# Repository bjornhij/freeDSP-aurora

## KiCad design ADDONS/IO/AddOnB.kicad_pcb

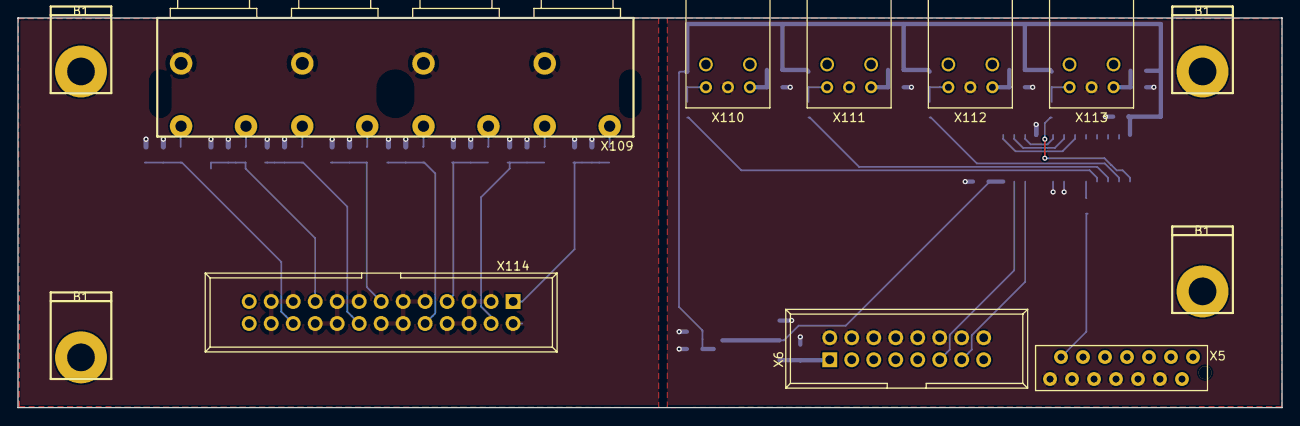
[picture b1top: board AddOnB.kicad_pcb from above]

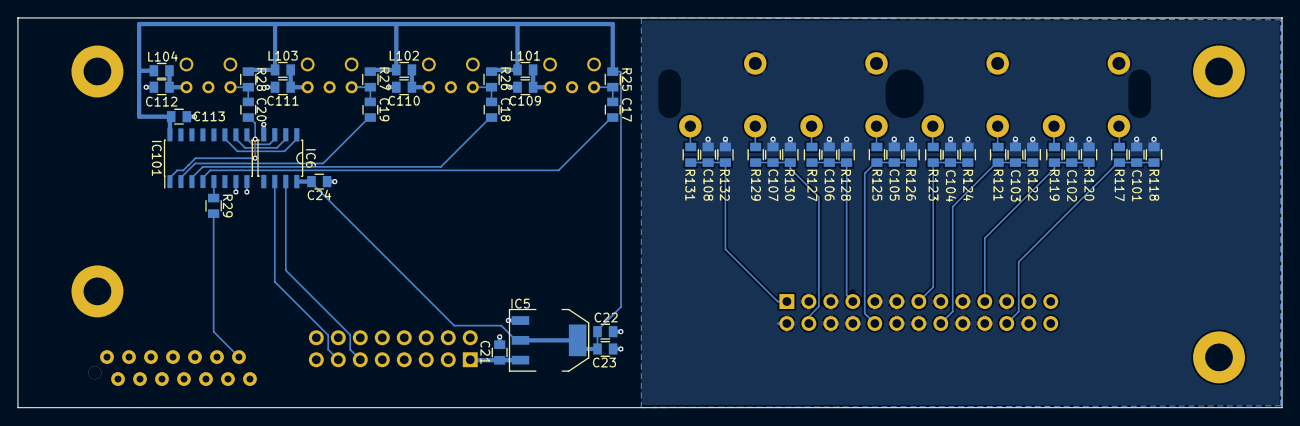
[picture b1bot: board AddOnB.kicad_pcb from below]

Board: 2 copper layers, 146.0 x 45.0 mm, 61 parts (49 on the bottom side), 38 nets.

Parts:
B1, B1#2, B1#3, B1#4: Montagewinkel
C17, C18, C19, C20: CAP_10n0_50V_X7R_0805; C0805-X7R
C21, C23: CAP_10u0_25V_X5R_0805; C0805-X7R
C22, C24, C109, C110, C111, C112, C113: CAP_100n_50V_X7R_0805; C0805-X7R
C101, C102, C103, C104, C105, C106, C107, C108: CAP_100p_50V_C0G_NP0_0805; C0805-X7R
IC5: IC_NCP1117LPST33; SOT223
IC6: PCA9536D; SOIC8_3.9x4.9mm_Pitch1.27mm
IC101: 74HC251; SOIC-16_3.9x9.9mm_P1.27mm
L101, L102, L103, L104: 47u0; C0805-X7R
R25, R26, R27, R28: RES_10K0_1%_0.125W_Thick_0805; C0805-RES
R29: RES_33R0_1%_0.125W_Thick_0805; C0805-RES
R117, R119, R121, R123, R125, R127, R129, R131: RES_100R_1%_0.25W_Thin_0805; C0805-RES
R118, R120, R122, R124, R126, R128, R130, R132: RES_220K_1%_0.125W_Thick_0805; C0805-RES
X5: MicroMatch14; MM-14G
X6: HDR_02x08; IDC2x8_Pitch2.54mm
X109: CONN_RCA_02x04; PJRAS4X2U01
X110, X111, X112, X113: PLR135_T10
X114: CON_IDC26; IDC26

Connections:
+3V3: C22.1, C23.1, C24.2, C113.2, IC5.2, IC5.4, IC6.8, IC101.16, L101.1, L102.1, L103.1, L104.1, R25.2, R26.2, R27.2, R28.2
+12V: C21.1, IC5.3, X6.1
/AIN1+: C101.1, R117.2, R118.2, X114.22
/AIN2+: C102.1, R119.2, R120.2, X114.19
/AIN3+: C103.1, R121.2, R122.2, X114.16
/AIN4+: C104.1, R123.2, R124.2, X114.13
/AIN5+: C105.1, R125.2, R126.2, X114.10
/AIN6+: C106.1, R127.2, R128.2, X114.7
/AIN7+: C107.1, R129.2, R130.2, X114.4
/AIN8+: C108.1, R131.2, R132.2, X114.1
/SCL: IC6.6, X6.13
/SDA: IC6.7, X6.11
/SPDIF_RX: R29.2, X5.13
GND: C21.2, C22.2, C23.2, C24.1, C101.2, C102.2, C103.2, C104.2, C105.2, C106.2, C107.2, C108.2, C109.2, C110.2, C111.2, C112.2, C113.1, IC5.1, IC6.4, IC101.7, IC101.8, R118.1, R120.1, R122.1, R124.1, R126.1, R128.1, R130.1, R132.1, X5.4, X5.6, X5.8, X5.10, X5.12, X5.14, X6.2, X6.4, X6.6, X6.8, X6.10, X6.12, X6.14, X6.16, X109.3A, X109.3B, X109.3C, X109.3D, X110.2, X111.2, X112.2, X113.2, X114.2, X114.3, X114.5, X114.6, X114.8, X114.9, X114.11, X114.12, X114.14, X114.15, X114.17, X114.18, X114.20, X114.21, X114.23, X114.24
unnamed: C17.1, R25.1, X110.3
unnamed: C17.2, IC101.4
unnamed: C18.1, R26.1, X111.3
unnamed: C18.2, IC101.3
unnamed: C19.1, R27.1, X112.3
unnamed: C19.2, IC101.2
unnamed: C20.1, R28.1, X113.3
unnamed: C20.2, IC101.1
unnamed: C109.1, L101.2, X110.1
unnamed: C110.1, L102.2, X111.1
unnamed: C111.1, L103.2, X112.1
unnamed: C112.1, L104.2, X113.1
unnamed: IC101.5, R29.1
unnamed: IC6.3, IC101.9
unnamed: IC6.2, IC101.10
unnamed: IC6.1, IC101.11
unnamed: R117.1, X109.2A
unnamed: R119.1, X109.1A
unnamed: R121.1, X109.2B
unnamed: R123.1, X109.1B
unnamed: R125.1, X109.2C
unnamed: R127.1, X109.1C
unnamed: R129.1, X109.2D
unnamed: R131.1, X109.1D

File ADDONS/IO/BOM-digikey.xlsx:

Reference | Value | Footprint | Datasheet | Manufacturer | pn | Value1 | Value2 | digikey
X5 | MicroMatch14 | rklib:MM-14G | ~ | TE Connectivity AMP Connectors | 1-215079-4 | MicroMatch-14 | -
X6 | HDR_02x08 | rklib:IDC2x8_Pitch2.54mm | ~ | On Shore Technology Inc. | 302-S161
X114 | CON_IDC26 | rklib:IDC26 | ~ | Bud Industries | BC-32677 | IDC26 |  | 377-2269-ND
C101 | CAP_100p_50V_C0G_NP0_0805 | rklib:C0805-X7R |  | KEMET | C0805C101J5GACTU | 100p | 5% 50V C0G/NP0 | 399-1122-1-ND
C102 | CAP_100p_50V_C0G_NP0_0805 | rklib:C0805-X7R |  | KEMET | C0805C101J5GACTU | 100p | 5% 50V C0G/NP0 | 399-1122-1-ND
C103 | CAP_100p_50V_C0G_NP0_0805 | rklib:C0805-X7R |  | KEMET | C0805C101J5GACTU | 100p | 5% 50V C0G/NP0 | 399-1122-1-ND
C104 | CAP_100p_50V_C0G_NP0_0805 | rklib:C0805-X7R |  | KEMET | C0805C101J5GACTU | 100p | 5% 50V C0G/NP0 | 399-1122-1-ND
C105 | CAP_100p_50V_C0G_NP0_0805 | rklib:C0805-X7R |  | KEMET | C0805C101J5GACTU | 100p | 5% 50V C0G/NP0 | 399-1122-1-ND
C106 | CAP_100p_50V_C0G_NP0_0805 | rklib:C0805-X7R |  | KEMET | C0805C101J5GACTU | 100p | 5% 50V C0G/NP0 | 399-1122-1-ND
C107 | CAP_100p_50V_C0G_NP0_0805 | rklib:C0805-X7R |  | KEMET | C0805C101J5GACTU | 100p | 5% 50V C0G/NP0 | 399-1122-1-ND
C108 | CAP_100p_50V_C0G_NP0_0805 | rklib:C0805-X7R |  | KEMET | C0805C101J5GACTU | 100p | 5% 50V C0G/NP0 | 399-1122-1-ND
C109 | CAP_100n_50V_X7R_0805 | rklib:C0805-X7R |  | KEMET | C0805C104K5RACTU | 100n | 5% 50V X7R | 399-1170-1-ND
C110 | CAP_100n_50V_X7R_0805 | rklib:C0805-X7R |  | KEMET | C0805C104K5RACTU | 100n | 5% 50V X7R | 399-1170-1-ND
C111 | CAP_100n_50V_X7R_0805 | rklib:C0805-X7R |  | KEMET | C0805C104K5RACTU | 100n | 5% 50V X7R | 399-1170-1-ND
C112 | CAP_100n_50V_X7R_0805 | rklib:C0805-X7R |  | KEMET | C0805C104K5RACTU | 100n | 5% 50V X7R | 399-1170-1-ND
C113 | CAP_100n_50V_X7R_0805 | rklib:C0805-X7R |  | KEMET | C0805C104K5RACTU | 100n | 5% 50V X7R | 399-1170-1-ND
C22 | CAP_100n_50V_X7R_0805 | rklib:C0805-X7R |  | KEMET | C0805C104K5RACTU | 100n | 5% 50V X7R | 399-1170-1-ND
C24 | CAP_100n_50V_X7R_0805 | rklib:C0805-X7R |  | KEMET | C0805C104K5RACTU | 100n | 5% 50V X7R | 399-1170-1-ND
C17 | CAP_10n0_50V_X7R_0805 | rklib:C0805-X7R |  | Yageo | CC0805KRX7R9BB103 | 10n0 | 10% 50V X7R | 311-1136-1-ND
C18 | CAP_10n0_50V_X7R_0805 | rklib:C0805-X7R |  | Yageo | CC0805KRX7R9BB103 | 10n0 | 10% 50V X7R | 311-1136-1-ND
C19 | CAP_10n0_50V_X7R_0805 | rklib:C0805-X7R |  | Yageo | CC0805KRX7R9BB103 | 10n0 | 10% 50V X7R | 311-1136-1-ND
C20 | CAP_10n0_50V_X7R_0805 | rklib:C0805-X7R |  | Yageo | CC0805KRX7R9BB103 | 10n0 | 10% 50V X7R | 311-1136-1-ND
C21 | CAP_10u0_25V_X5R_0805 | rklib:C0805-X7R |  | Murata Electronics North America | GRM21BR61E106MA73L | 10u0 | 20% 25V X5R | 490-10748-1-ND
C23 | CAP_10u0_25V_X5R_0805 | rklib:C0805-X7R |  | Murata Electronics North America | GRM21BR61E106MA73L | 10u0 | 20% 25V X5R | 490-10748-1-ND
L101 | 47u0 | rklib:C0805-X7R |  | Taiyo Yuden | LBR2012T470K
L102 | 47u0 | rklib:C0805-X7R |  | Taiyo Yuden | LBR2012T470K
L103 | 47u0 | rklib:C0805-X7R |  | Taiyo Yuden | LBR2012T470K
L104 | 47u0 | rklib:C0805-X7R |  | Taiyo Yuden | LBR2012T470K
IC5 | IC_NCP1117LPST33 | rklib:SOT223 |  | ON Semiconductor | NCP1117LPST33T3G | NCP1117LPST33 | LDO | NCP1117LPST33T3GOSCT-ND
IC6 | PCA9536D | rklib:SOIC8_3.9x4.9mm_Pitch1.27mm | http://www.nxp.com/documents/data_sheet/PCA9536.pdf | Texas Instruments | PCA9536DR
X109 | CONN_RCA_02x04 | rklib:PJRAS4X2U01 |  | Switchcraft Inc. | PJRAS4X2U01AUX
X110 | PLR135_T10 | rklib:PLR135_T10 |  | Everlight Electronics Co Ltd | PLR135/T10
X111 | PLR135_T10 | rklib:PLR135_T10 |  | Everlight Electronics Co Ltd | PLR135/T10
X112 | PLR135_T10 | rklib:PLR135_T10 |  | Everlight Electronics Co Ltd | PLR135/T10
X113 | PLR135_T10 | rklib:PLR135_T10 |  | Everlight Electronics Co Ltd | PLR135/T10
R25 | RES_10K0_1%_0.125W_Thick_0805 | rklib:C0805-RES |  | Yageo | RC0805FR-0710KL | 10K0 | 1% 0.125W Thick | 311-10.0KCRCT-ND
R26 | RES_10K0_1%_0.125W_Thick_0805 | rklib:C0805-RES |  | Yageo | RC0805FR-0710KL | 10K0 | 1% 0.125W Thick | 311-10.0KCRCT-ND
R27 | RES_10K0_1%_0.125W_Thick_0805 | rklib:C0805-RES |  | Yageo | RC0805FR-0710KL | 10K0 | 1% 0.125W Thick | 311-10.0KCRCT-ND
R28 | RES_10K0_1%_0.125W_Thick_0805 | rklib:C0805-RES |  | Yageo | RC0805FR-0710KL | 10K0 | 1% 0.125W Thick | 311-10.0KCRCT-ND
R118 | RES_220K_1%_0.125W_Thick_0805 | rklib:C0805-RES |  | Yageo | RC0805FR-07220KL | 220K | 1% 0.125W Thick
R120 | RES_220K_1%_0.125W_Thick_0805 | rklib:C0805-RES |  | Yageo | RC0805FR-07220KL | 220K | 1% 0.125W Thick
R122 | RES_220K_1%_0.125W_Thick_0805 | rklib:C0805-RES |  | Yageo | RC0805FR-07220KL | 220K | 1% 0.125W Thick
R124 | RES_220K_1%_0.125W_Thick_0805 | rklib:C0805-RES |  | Yageo | RC0805FR-07220KL | 220K | 1% 0.125W Thick
R126 | RES_220K_1%_0.125W_Thick_0805 | rklib:C0805-RES |  | Yageo | RC0805FR-07220KL | 220K | 1% 0.125W Thick
R128 | RES_220K_1%_0.125W_Thick_0805 | rklib:C0805-RES |  | Yageo | RC0805FR-07220KL | 220K | 1% 0.125W Thick
R130 | RES_220K_1%_0.125W_Thick_0805 | rklib:C0805-RES |  | Yageo | RC0805FR-07220KL | 220K | 1% 0.125W Thick
R132 | RES_220K_1%_0.125W_Thick_0805 | rklib:C0805-RES |  | Yageo | RC0805FR-07220KL | 220K | 1% 0.125W Thick
R29 | RES_33R0_1%_0.125W_Thick_0805 | rklib:C0805-RES |  | Yageo | RC0805FR-0733RL | 33R0 | 1% 0.125W Thick | 311-33.0CRCT-ND
R117 | RES_100R_1%_0.25W_Thin_0805 | rklib:C0805-RES |  | Stackpole Electronics Inc | RNCP0805FTD100R | 100R | 1% 0.25W Thin | RNCP0805FTD100RCT-ND
R119 | RES_100R_1%_0.25W_Thin_0805 | rklib:C0805-RES |  | Stackpole Electronics Inc | RNCP0805FTD100R | 100R | 1% 0.25W Thin | RNCP0805FTD100RCT-ND
R121 | RES_100R_1%_0.25W_Thin_0805 | rklib:C0805-RES |  | Stackpole Electronics Inc | RNCP0805FTD100R | 100R | 1% 0.25W Thin | RNCP0805FTD100RCT-ND
R123 | RES_100R_1%_0.25W_Thin_0805 | rklib:C0805-RES |  | Stackpole Electronics Inc | RNCP0805FTD100R | 100R | 1% 0.25W Thin | RNCP0805FTD100RCT-ND
R125 | RES_100R_1%_0.25W_Thin_0805 | rklib:C0805-RES |  | Stackpole Electronics Inc | RNCP0805FTD100R | 100R | 1% 0.25W Thin | RNCP0805FTD100RCT-ND
R127 | RES_100R_1%_0.25W_Thin_0805 | rklib:C0805-RES |  | Stackpole Electronics Inc | RNCP0805FTD100R | 100R | 1% 0.25W Thin | RNCP0805FTD100RCT-ND
R129 | RES_100R_1%_0.25W_Thin_0805 | rklib:C0805-RES |  | Stackpole Electronics Inc | RNCP0805FTD100R | 100R | 1% 0.25W Thin | RNCP0805FTD100RCT-ND
R131 | RES_100R_1%_0.25W_Thin_0805 | rklib:C0805-RES |  | Stackpole Electronics Inc | RNCP0805FTD100R | 100R | 1% 0.25W Thin | RNCP0805FTD100RCT-ND
IC101 | 74HC251 | Package_SO:SOIC-16_3.9x9.9mm_P1.27mm |  | Texas Instruments | SN74HC251DR
B1 | Montagewinkel | rklib:Montagewinkel | ~
B3 | Montagewinkel | rklib:Montagewinkel | ~
B2 | Montagewinkel | rklib:Montagewinkel | ~
B4 | Montagewinkel | rklib:Montagewinkel | ~

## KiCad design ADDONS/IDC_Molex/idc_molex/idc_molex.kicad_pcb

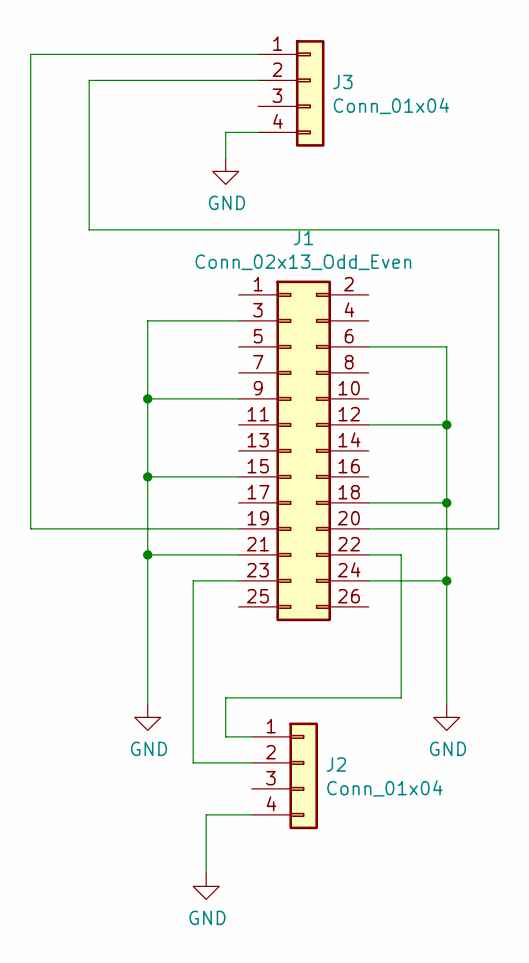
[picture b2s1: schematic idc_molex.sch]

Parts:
J1: Conn_02x13_Odd_Even; PinSocket_2x13_P2.54mm_Vertical
J2, J3: Conn_01x04; Molex_Micro-Fit_3.0_43045-0400_2x02_P3.00mm_Horizontal

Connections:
GND: J1.3, J1.6, J1.9, J1.12, J1.15, J1.18, J1.21, J1.24, J2.4, J3.4
unnamed: J1.19, J3.1
unnamed: J1.20, J3.2
unnamed: J1.22, J2.1
unnamed: J1.23, J2.2

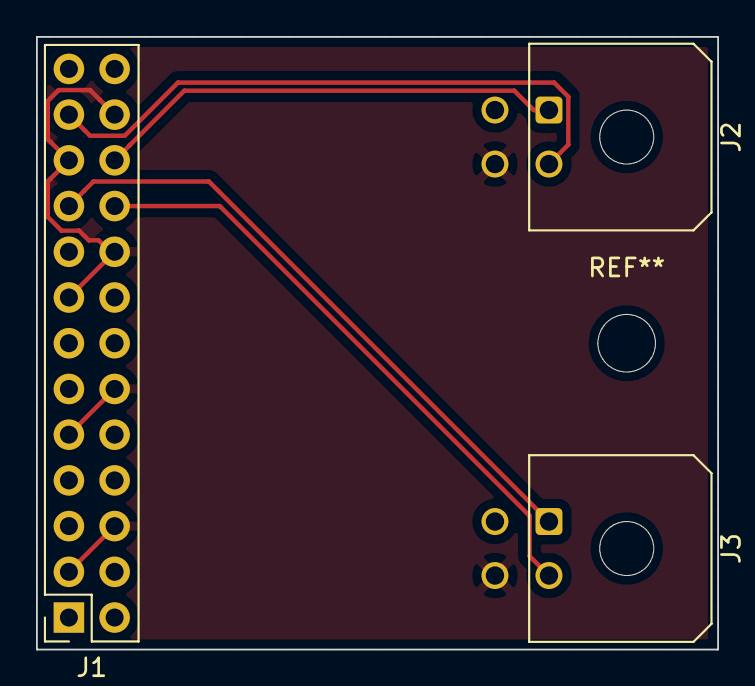
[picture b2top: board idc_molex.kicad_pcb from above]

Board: 2 copper layers, 37.8 x 34.0 mm, 3 parts (0 on the bottom side), 5 nets.

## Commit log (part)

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2019-09-07 initial
2019-11-15 Start serial
